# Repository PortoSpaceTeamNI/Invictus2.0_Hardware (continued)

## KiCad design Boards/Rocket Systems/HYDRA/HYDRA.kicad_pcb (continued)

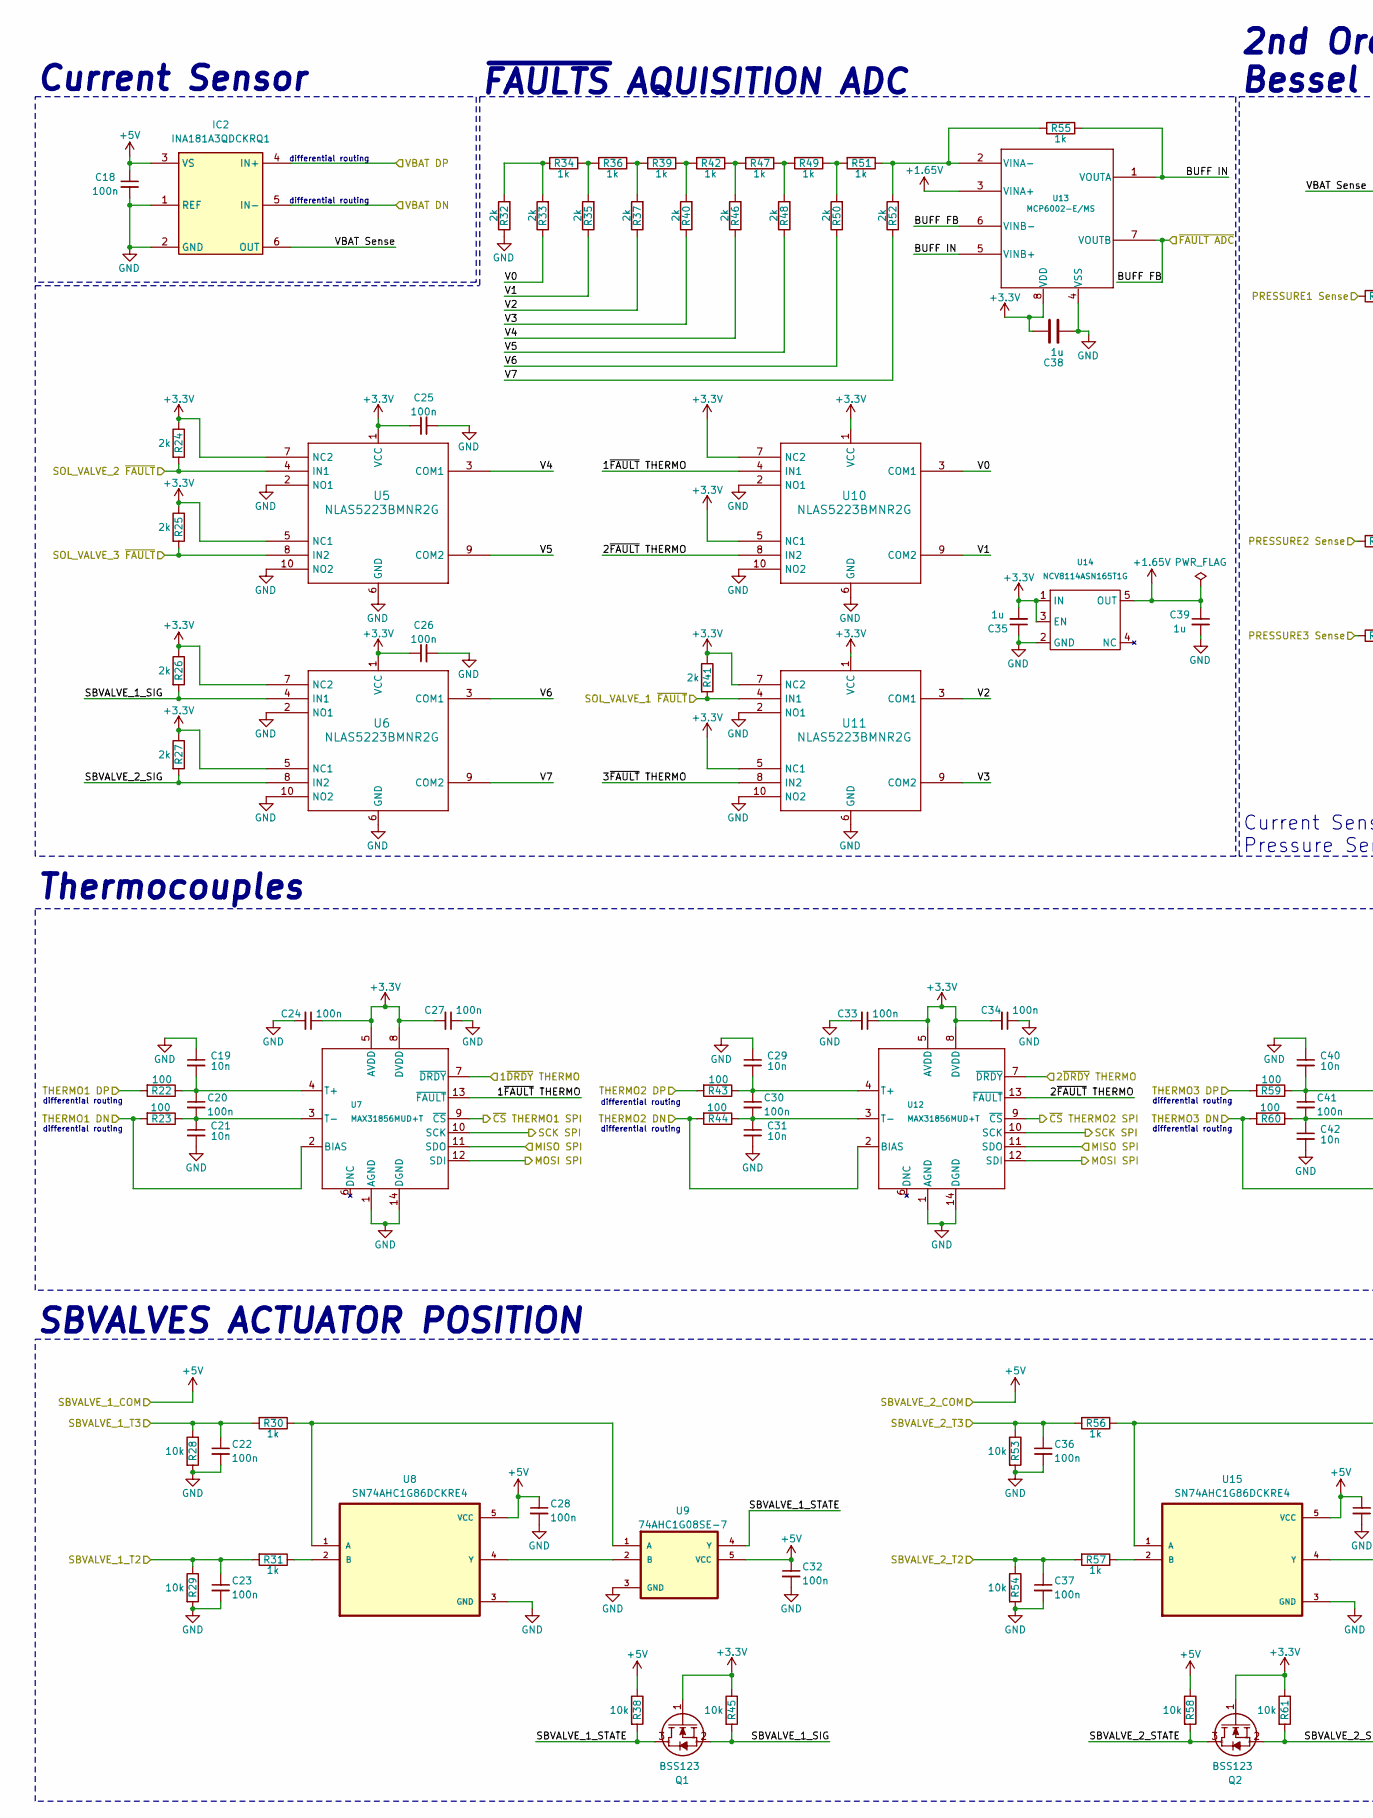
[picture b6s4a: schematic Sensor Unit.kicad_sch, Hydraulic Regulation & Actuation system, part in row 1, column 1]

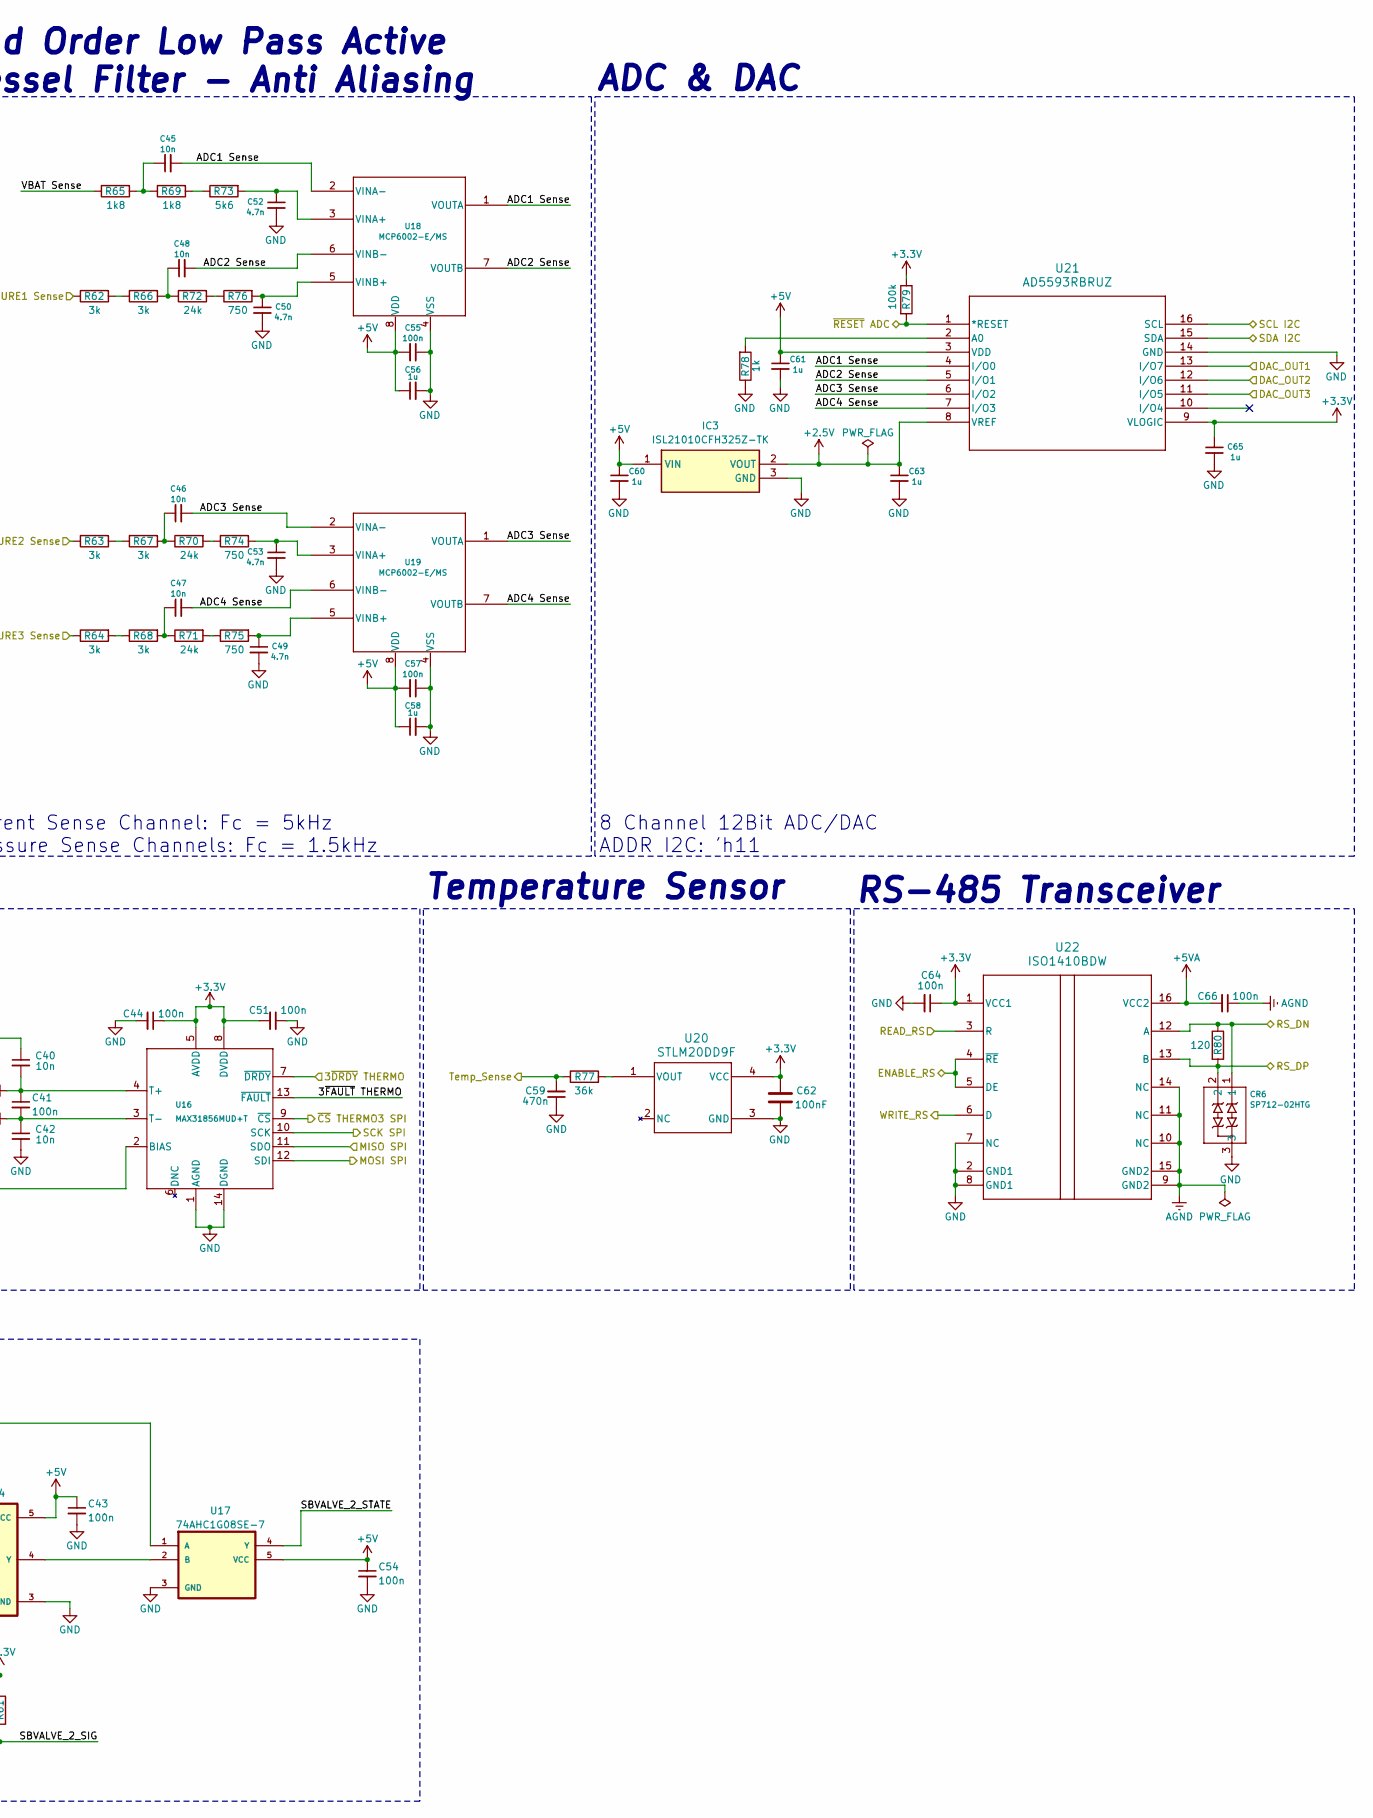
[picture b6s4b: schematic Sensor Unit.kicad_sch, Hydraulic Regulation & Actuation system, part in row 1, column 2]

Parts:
C18, C20, C22, C23, C24, C25, C26, C27, C28, C30, C32, C33, C34, C36, C37, C41, C43, C44, C51, C54, C55, C57, C64, C66: 100n; Capacitor_0402
C19, C21, C29, C31, C40, C42, C45, C46, C47, C48: 10n; Capacitor_0402
C35, C38, C39, C56, C58, C60, C61, C63, C65: 1u; Capacitor_0603
C49, C50, C52, C53: 4.7n; Capacitor_0402
C59: 470n; Capacitor_0402
C62: 100nF; Capacitor_0402
CR6: SP712-02HTG; SOT23-3_LTF
IC2: INA181A3QDCKRQ1; SOT65P210X110-6N; Mouser Part Number 595-INA181A3QDCKRQ1
IC3: ISL21010CFH325Z-TK; SOT95P237X112-3N; Mouser Part Number 968-ISL21010CFH325ZT
Q1, Q2: BSS123; SOT96P237X111-3N; Mouser Part Number 512-BSS123
R22, R23, R43, R44, R59, R60: 100; RES_0402
R24, R25, R26, R27, R32, R33, R35, R37, R40, R41, R46, R48, R50, R52: 2k; RES_0402
R28, R29, R38, R45, R53, R54, R58, R61: 10k; RES_0402
R30, R31, R34, R36, R39, R42, R47, R49, R51, R55, R56, R57, R78: 1k; RES_0402
R62, R63, R64, R66, R67, R68: 3k; RES_0402
R65, R69: 1k8; RES_0402
R70, R71, R72: 24k; RES_0402
R73: 5k6; RES_0402
R74, R75, R76: 750; RES_0402
R77: 36k; RES_0402
R79: 100k; RES_0402
R80: 120; RES_0603
U5, U6, U10, U11: NLAS5223BMNR2G; WQFN10_1P4X1P8_ONS
U7, U12, U16: MAX31856MUD+T; 21-0066J_14_MXM
U8, U15: SN74AHC1G86DCKRE4; SOT65P210X110-5N
U9, U17: 74AHC1G08SE-7; SOT65P210X110-5N; MPN 74AHC1G08SE-7
U13, U18, U19: MCP6002-E/MS; MSOP8_MC_MCH
U14: NCV8114ASN165T1G; SOT95P275X120-5N
U20: STLM20DD9F; UDFN-4L_STM
U21: AD5593RBRUZ; RU-16_ADI-L
U22: ISO1410BDW; DW0016B_L

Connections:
+1.65V: C39.1, U13.3 (VINA+), U14.5 (OUT)
+2.5V: C63.1, IC3.2 (VOUT), U21.8 (VREF)
+3.3V: C24.1, C25.1, C26.1, C27.2, C33.1, C34.2, C35.2, C38.1, C44.1, C51.2, C62.1, C64.1, C65.1, Q1.1 (G), Q2.1 (G), R24.1, R25.1, R26.1, R27.1, R41.1, R45.1, R61.1, R79.1, U5.1 (VCC), U5.5 (NC1), U5.7 (NC2), U6.1 (VCC), U6.5 (NC1), U6.7 (NC2), U7.5 (AVDD), U7.8 (DVDD), U10.1 (VCC), U10.5 (NC1), U10.7 (NC2), U11.1 (VCC), U11.5 (NC1), U11.7 (NC2), U12.5 (AVDD), U12.8 (DVDD), U13.8 (VDD), U14.1 (IN), U14.3 (EN), U16.5 (AVDD), U16.8 (DVDD), U20.4 (VCC), U21.9 (VLOGIC), U22.1 (VCC1); also elsewhere on the board
+5V: C18.1, C28.1, C32.1, C43.1, C54.1, C55.2, C56.1, C57.2, C58.1, C60.1, C61.1, IC2.3 (VS), IC3.1 (VIN), R38.1, R58.1, U8.5 (VCC), U9.5 (VCC), U15.5 (VCC), U17.5 (VCC), U18.8 (VDD), U19.8 (VDD), U21.3 (VDD); also elsewhere on the board
+5VA: C66.2, U22.16 (VCC2); also elsewhere on the board
/1~DRDY THERMO: U7.7 (~DRDY); also elsewhere on the board
/2~DRDY THERMO: U12.7 (~DRDY); also elsewhere on the board
/3~DRDY THERMO: U16.7 (~DRDY); also elsewhere on the board
/Actuation Unit/SOL_VALVE_1 DUTY: U21.13 (I/O7); also elsewhere on the board
/Actuation Unit/SOL_VALVE_1 ~FAULT: R25.2, U5.8 (IN2); also elsewhere on the board
/Actuation Unit/SOL_VALVE_2 DUTY: U21.12 (I/O6); also elsewhere on the board
/Actuation Unit/SOL_VALVE_2 ~FAULT: R24.2, U5.4 (IN1); also elsewhere on the board
/Actuation Unit/SOL_VALVE_3 DUTY: U21.11 (I/O5); also elsewhere on the board
/Actuation Unit/SOL_VALVE_3 ~FAULT: R41.2, U11.4 (IN1); also elsewhere on the board
/ENABLE_RS: U22.4 (~RE), U22.5 (DE); also elsewhere on the board
/IO Connectors/PRESSURE1 Sense: R62.1; also elsewhere on the board
/IO Connectors/PRESSURE2 Sense: R63.1; also elsewhere on the board
/IO Connectors/PRESSURE3 Sense: R64.1; also elsewhere on the board
/IO Connectors/RS_DN: CR6.1, R80.1, U22.12 (A); also elsewhere on the board
/IO Connectors/RS_DP: CR6.2, R80.2, U22.13 (B); also elsewhere on the board
/IO Connectors/SBVALVE_1_T2: C23.1, R29.1, R31.2; also elsewhere on the board
/IO Connectors/SBVALVE_1_T3: C22.1, R28.1, R30.2; also elsewhere on the board
/IO Connectors/SBVALVE_2_T2: C37.1, R54.1, R57.2; also elsewhere on the board
/IO Connectors/SBVALVE_2_T3: C36.1, R53.1, R56.2; also elsewhere on the board
/IO Connectors/THERMO1 DN: R23.2, U7.2 (BIAS); also elsewhere on the board
/IO Connectors/THERMO1 DP: R22.2; also elsewhere on the board
/IO Connectors/THERMO2 DN: R44.2, U12.2 (BIAS); also elsewhere on the board
/IO Connectors/THERMO2 DP: R43.2; also elsewhere on the board
/IO Connectors/THERMO3 DN: R60.2, U16.2 (BIAS); also elsewhere on the board
/IO Connectors/THERMO3 DP: R59.2; also elsewhere on the board
/MISO SPI: U7.11 (SDO), U12.11 (SDO), U16.11 (SDO); also elsewhere on the board
/MOSI SPI: U7.12 (SDI), U12.12 (SDI), U16.12 (SDI); also elsewhere on the board
/PCB Temperature Sense: C59.2, R77.1; also elsewhere on the board
/Power Unit/VBAT DP: IC2.4 (IN+); also elsewhere on the board
/READ_RS: U22.3 (R); also elsewhere on the board
/RP2040 Standard/GP14/I2C1 SDA: U21.15 (SDA); also elsewhere on the board
/RP2040 Standard/GP15/I2C1 SCL: U21.16 (SCL); also elsewhere on the board
/RP2040 Standard/GPIO16: R79.2, U21.1 (*RESET); also elsewhere on the board
/SCK SPI: U7.10 (SCK), U12.10 (SCK), U16.10 (SCK); also elsewhere on the board
/Sensor Unit/1~FAULT THERMO: U7.13 (~FAULT), U10.4 (IN1)
/Sensor Unit/2~FAULT THERMO: U10.8 (IN2), U12.13 (~FAULT)
/Sensor Unit/3~FAULT THERMO: U11.8 (IN2), U16.13 (~FAULT)
/Sensor Unit/ADC1 Sense: C45.2, U18.1 (VOUTA), U18.2 (VINA-), U21.4 (I/O0)
/Sensor Unit/ADC2 Sense: C48.2, U18.6 (VINB-), U18.7 (VOUTB), U21.5 (I/O1)
/Sensor Unit/ADC3 Sense: C46.2, U19.1 (VOUTA), U19.2 (VINA-), U21.6 (I/O2)
/Sensor Unit/ADC4 Sense: C47.2, U19.6 (VINB-), U19.7 (VOUTB), U21.7 (I/O3)
/Sensor Unit/BUFF FB: U13.6 (VINB-), U13.7 (VOUTB); also elsewhere on the board
/Sensor Unit/BUFF IN: R55.1, U13.1 (VOUTA), U13.5 (VINB+)
/Sensor Unit/SBVALVE_1_SIG: Q1.2 (S), R26.2, R45.2, U6.4 (IN1)
/Sensor Unit/SBVALVE_1_STATE: Q1.3 (D), R38.2, U9.4 (Y)
/Sensor Unit/SBVALVE_2_SIG: Q2.2 (S), R27.2, R61.2, U6.8 (IN2)
/Sensor Unit/SBVALVE_2_STATE: Q2.3 (D), R58.2, U17.4 (Y)
/Sensor Unit/V0: R33.1, U10.3 (COM1)
/Sensor Unit/V1: R35.1, U10.9 (COM2)
/Sensor Unit/V2: R37.1, U11.3 (COM1)
/Sensor Unit/V3: R40.1, U11.9 (COM2)
/Sensor Unit/V4: R46.1, U5.3 (COM1)
/Sensor Unit/V5: R48.1, U5.9 (COM2)
/Sensor Unit/V6: R50.1, U6.3 (COM1)
/Sensor Unit/V7: R52.1, U6.9 (COM2)
/Sensor Unit/VBAT Sense: IC2.6 (OUT), R65.1
/WRITE_RS: U22.6 (D); also elsewhere on the board
/~CS THERMO1 SPI: U7.9 (~CS); also elsewhere on the board
/~CS THERMO2 SPI: U12.9 (~CS); also elsewhere on the board
/~CS THERMO3 SPI: U16.9 (~CS); also elsewhere on the board
AGND: C66.1, U22.9 (GND2), U22.10 (NC), U22.11 (NC), U22.14 (NC), U22.15 (GND2); also elsewhere on the board
GND: C18.2, C19.1, C21.2, C22.2, C23.2, C24.2, C25.2, C26.2, C27.1, C28.2, C29.1, C31.2, C32.2, C33.2, C34.1, C35.1, C36.2, C37.2, C38.2, C39.2, C40.1, C42.2, C43.2, C44.2, C49.2, C50.2, C51.1, C52.2, C53.2, C54.2, C55.1, C56.2, C57.1, C58.2, C59.1, C60.2, C61.2, C62.2, C63.2, C64.2, C65.2, CR6.3, IC2.1 (REF), IC2.2 (GND), IC3.3 (GND), R28.2, R29.2, R32.1, R53.2, R54.2, R78.1, U5.2 (NO1), U5.6 (GND), U5.10 (NO2), U6.2 (NO1), U6.6 (GND), U6.10 (NO2), U7.1 (AGND), U7.14 (DGND), U8.3 (GND), U9.3 (GND), U10.2 (NO1), U10.6 (GND), U10.10 (NO2), U11.2 (NO1), U11.6 (GND), U11.10 (NO2), U12.1 (AGND), U12.14 (DGND), U13.4 (VSS), U14.2 (GND), U15.3 (GND), U16.1 (AGND), U16.14 (DGND), U17.3 (GND), U18.4 (VSS), U19.4 (VSS), U20.3 (GND), U21.14 (GND), U22.2 (GND1), U22.7 (NC), U22.8 (GND1); also elsewhere on the board
unnamed: C45.1, R65.2, R69.1
unnamed: C46.1, R67.2, R70.1
unnamed: C47.1, R68.2, R71.1
unnamed: C48.1, R66.2, R72.1
unnamed: R32.2, R33.2, R34.2
unnamed: R34.1, R35.2, R36.2
unnamed: R36.1, R37.2, R39.2
unnamed: R39.1, R40.2, R42.2
unnamed: R42.1, R46.2, R47.2
unnamed: R47.1, R48.2, R49.2
unnamed: R49.1, R50.2, R51.2
unnamed: R62.2, R66.1
unnamed: R63.2, R67.1
unnamed: R64.2, R68.1
unnamed: R69.2, R73.1
unnamed: R70.2, R74.1
unnamed: R71.2, R75.1
unnamed: R72.2, R76.1
unnamed: C19.2, C20.1, R22.1, U7.4 (T+)
unnamed: C20.2, C21.1, R23.1, U7.3 (T-)
unnamed: R30.1, U8.1 (A), U9.1 (A)
unnamed: R31.1, U8.2 (B)
unnamed: U8.4 (Y), U9.2 (B)
unnamed: C29.2, C30.1, R43.1, U12.4 (T+)
unnamed: C30.2, C31.1, R44.1, U12.3 (T-)
unnamed: R51.1, R52.2, R55.2, U13.2 (VINA-)
unnamed: R56.1, U15.1 (A), U17.1 (A)
unnamed: R57.1, U15.2 (B)
unnamed: U15.4 (Y), U17.2 (B)
unnamed: C40.2, C41.1, R59.1, U16.4 (T+)
unnamed: C41.2, C42.1, R60.1, U16.3 (T-)
unnamed: C52.1, R73.2, U18.3 (VINA+)
unnamed: C50.1, R76.2, U18.5 (VINB+)
unnamed: C53.1, R74.2, U19.3 (VINA+)
unnamed: C49.1, R75.2, U19.5 (VINB+)
unnamed: R77.2, U20.1 (VOUT)
unnamed: R78.2, U21.2 (A0)
VDC: IC2.5 (IN-); also elsewhere on the board

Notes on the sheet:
differential routing
Current Sensor
SBVALVES ACTUATOR POSITION
8 Channel 12Bit ADC/DAC ADDR I2C: 'h11
Current Sense Channel: Fc = 5kHz Pressure Sense Channels: Fc = 1.5kHz
RS-485 Transceiver
~{FAULTS} AQUISITION ADC
Thermocouples
2nd Order Low Pass Active Bessel Filter - Anti Aliasing
ADC & DAC
Temperature Sensor

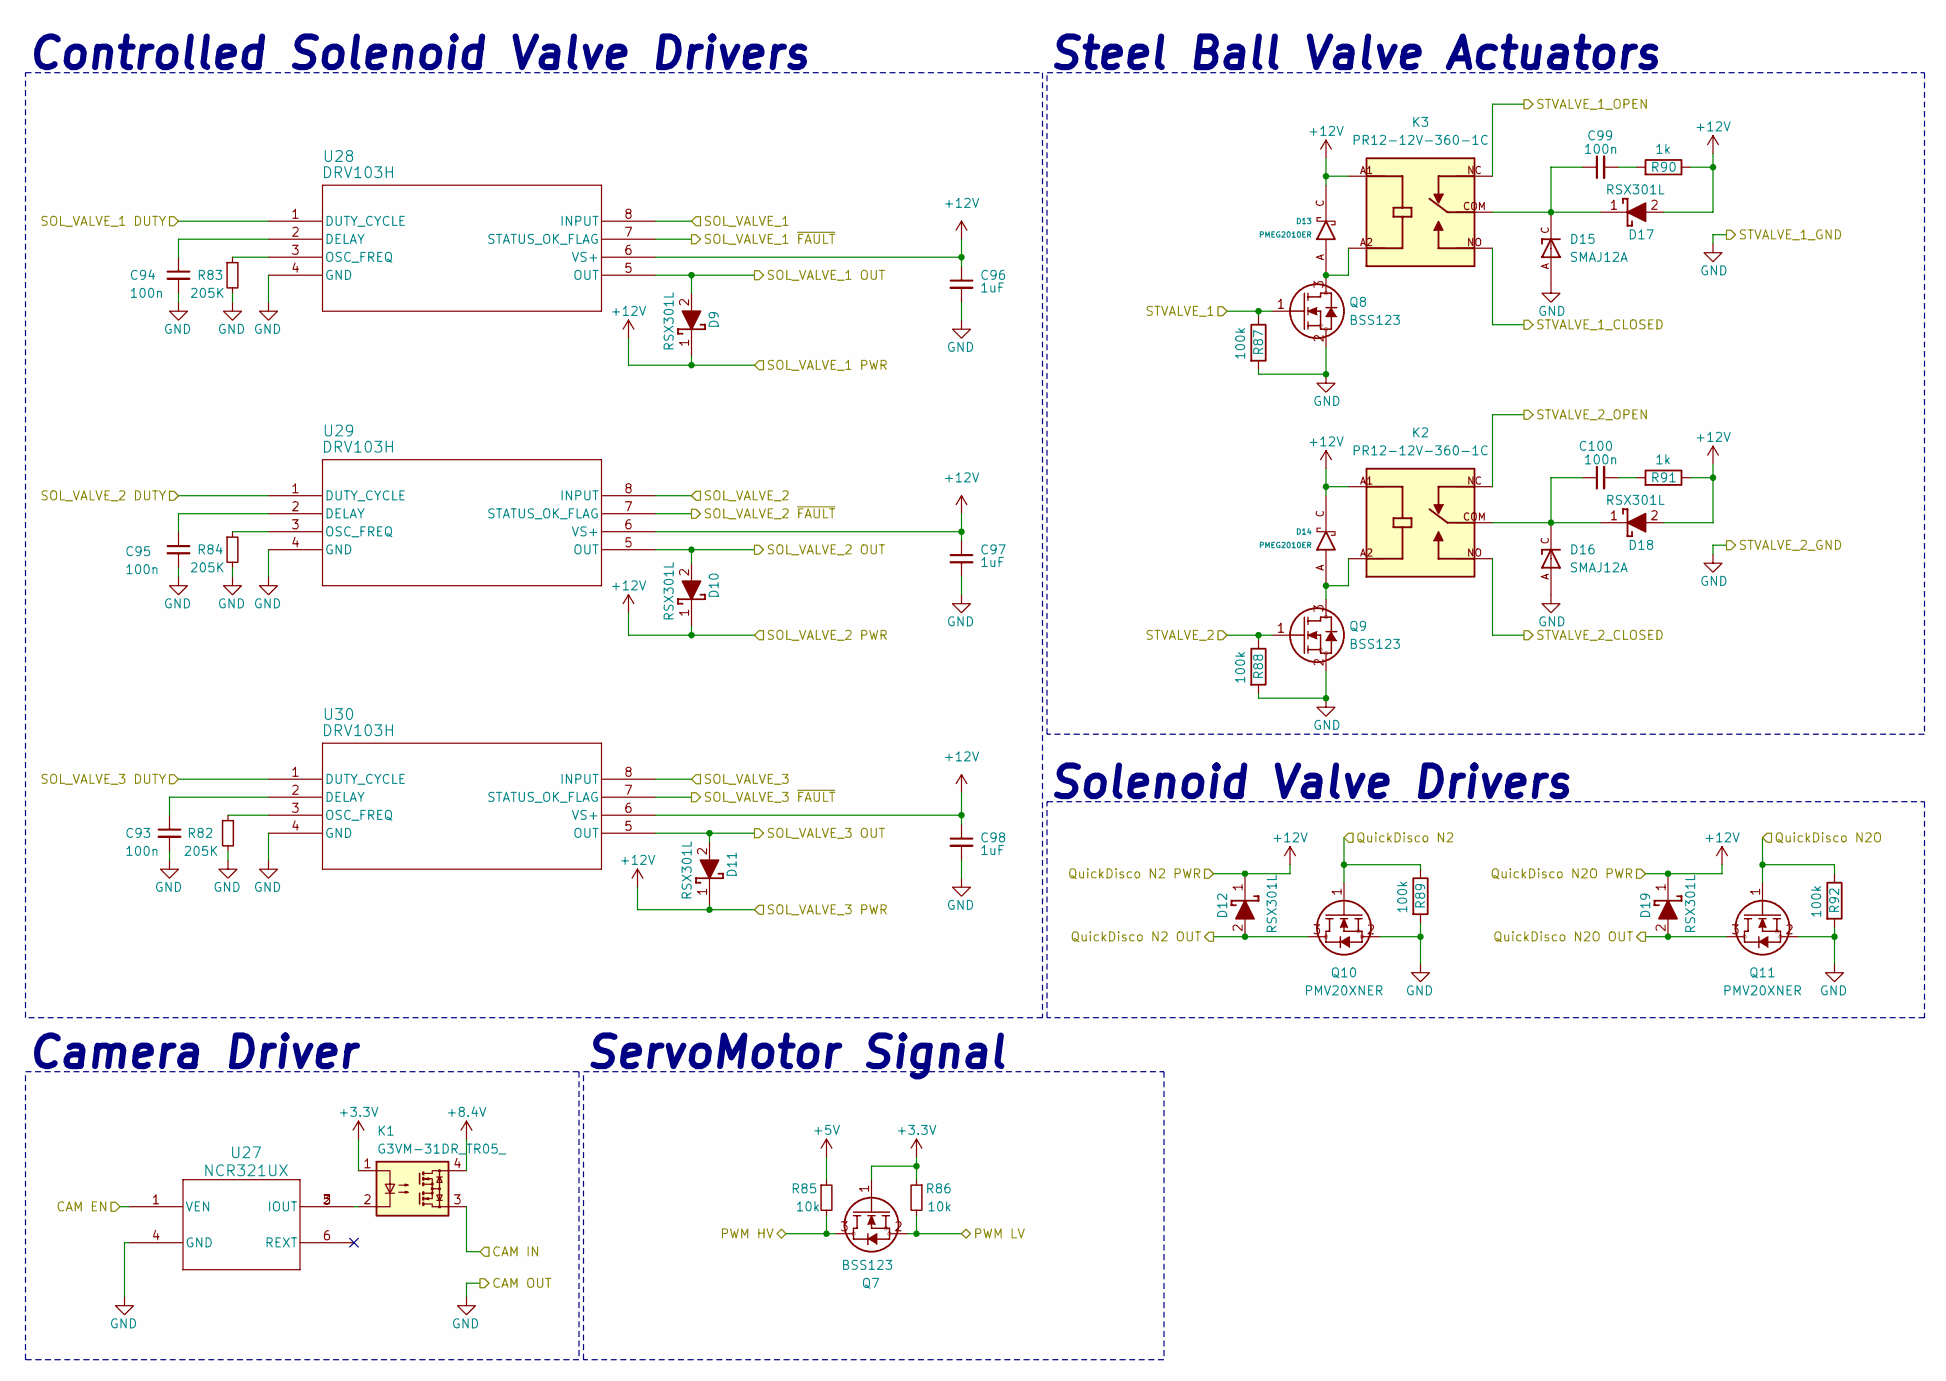
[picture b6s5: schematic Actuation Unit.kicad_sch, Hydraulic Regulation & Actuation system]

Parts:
C93, C94, C95: 100n; Capacitor_0402
C96, C97, C98: 1uF; Capacitor_0603
C99, C100: 100n; Capacitor_0603
D9, D10, D11, D12, D17, D18, D19: RSX301L; DIOM5026X220N; Mouser Part Number 755-RSX301L-30DDTE25
D13, D14: PMEG2010ER; SODFL3517X110N; PARTREV 01
D15, D16: SMAJ12A; DIOM4325X250N; PARTREV S2102
K1: G3VM-31DR_TR05_; G3VM31DRTR05; Mouser Part Number 653-G3VM-31DR(TR05)
K2, K3: PR12-12V-360-1C; RELAY_PR12-12V-360-1C; PARTREV 1.0
Q7, Q8, Q9: BSS123; SOT96P237X111-3N; Mouser Part Number 512-BSS123
Q10, Q11: PMV20XNER; SOT95P230X110-3N; Mouser Part Number 771-PMV20XNER
R82, R83, R84: 205K; RES_0402
R85, R86: 10k; RES_0402
R87, R88, R89, R92: 100k; RES_0402
R90, R91: 1k; RES_0805
U27: NCR321UX; TSOP6_SOT457_NEX
U28, U29, U30: DRV103H; DDA8-L

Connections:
+3.3V: K1.1, Q7.1 (G), R86.1; also elsewhere on the board
+5V: R85.1; also elsewhere on the board
+8.4V: K1.4; also elsewhere on the board
+12V: C96.1, C97.1, C98.1, D9.1 (K), D10.1 (K), D11.1 (K), D12.1 (K), D13.C, D14.C, D17.2 (A), D18.2 (A), D19.1 (K), K2.A1, K3.A1, R90.1, R91.1, U28.6 (VS+), U29.6 (VS+), U30.6 (VS+); also elsewhere on the board
/Actuation Unit/CAM EN: U27.1 (VEN); also elsewhere on the board
/Actuation Unit/CAM IN: K1.3; also elsewhere on the board
/Actuation Unit/PWM HV: Q7.3 (D), R85.2; also elsewhere on the board
/Actuation Unit/PWM LV: Q7.2 (S), R86.2; also elsewhere on the board
/Actuation Unit/QuickDisco N2: Q10.1 (G), R89.1; also elsewhere on the board
/Actuation Unit/QuickDisco N2 OUT: D12.2 (A), Q10.3 (D); also elsewhere on the board
/Actuation Unit/QuickDisco N2O: Q11.1 (G), R92.1; also elsewhere on the board
/Actuation Unit/QuickDisco N2O OUT: D19.2 (A), Q11.3 (D); also elsewhere on the board
/Actuation Unit/SOL_VALVE_1: U28.8 (INPUT); also elsewhere on the board
/Actuation Unit/SOL_VALVE_1 DUTY: U28.1 (DUTY_CYCLE); also elsewhere on the board
/Actuation Unit/SOL_VALVE_1 OUT: D9.2 (A), U28.5 (OUT); also elsewhere on the board
/Actuation Unit/SOL_VALVE_1 ~FAULT: U28.7 (STATUS_OK_FLAG); also elsewhere on the board
/Actuation Unit/SOL_VALVE_2: U29.8 (INPUT); also elsewhere on the board
/Actuation Unit/SOL_VALVE_2 DUTY: U29.1 (DUTY_CYCLE); also elsewhere on the board
/Actuation Unit/SOL_VALVE_2 OUT: D10.2 (A), U29.5 (OUT); also elsewhere on the board
/Actuation Unit/SOL_VALVE_2 ~FAULT: U29.7 (STATUS_OK_FLAG); also elsewhere on the board
/Actuation Unit/SOL_VALVE_3: U30.8 (INPUT); also elsewhere on the board
/Actuation Unit/SOL_VALVE_3 DUTY: U30.1 (DUTY_CYCLE); also elsewhere on the board
/Actuation Unit/SOL_VALVE_3 OUT: D11.2 (A), U30.5 (OUT); also elsewhere on the board
/Actuation Unit/SOL_VALVE_3 ~FAULT: U30.7 (STATUS_OK_FLAG); also elsewhere on the board
/Actuation Unit/STVALVE_1: Q8.1 (G), R87.1; also elsewhere on the board
/Actuation Unit/STVALVE_1_CLOSED: K3.NO; also elsewhere on the board
/Actuation Unit/STVALVE_1_OPEN: K3.NC; also elsewhere on the board
/Actuation Unit/STVALVE_2: Q9.1 (G), R88.1; also elsewhere on the board
/Actuation Unit/STVALVE_2_CLOSED: K2.NO; also elsewhere on the board
/Actuation Unit/STVALVE_2_OPEN: K2.NC; also elsewhere on the board
GND: C93.2, C94.2, C95.2, C96.2, C97.2, C98.2, D15.A, D16.A, Q8.2 (S), Q9.2 (S), Q10.2 (S), Q11.2 (S), R82.2, R83.2, R84.2, R87.2, R88.2, R89.2, R92.2, U27.4 (GND), U28.4 (GND), U29.4 (GND), U30.4 (GND); also elsewhere on the board
unnamed: C99.2, R90.2
unnamed: C100.2, R91.2
unnamed: C99.1, D15.C, D17.1 (K), K3.COM
unnamed: C100.1, D16.C, D18.1 (K), K2.COM
unnamed: K1.2, U27.2 (IOUT), U27.3 (IOUT), U27.5 (IOUT)
unnamed: D13.A, K3.A2, Q8.3 (D)
unnamed: D14.A, K2.A2, Q9.3 (D)
unnamed: C94.1, U28.2 (DELAY)
unnamed: R83.1, U28.3 (OSC_FREQ)
unnamed: C95.1, U29.2 (DELAY)
unnamed: R84.1, U29.3 (OSC_FREQ)
unnamed: C93.1, U30.2 (DELAY)
unnamed: R82.1, U30.3 (OSC_FREQ)

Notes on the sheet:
Solenoid Valve Drivers
Controlled Solenoid Valve Drivers
Camera Driver
ServoMotor Signal
Steel Ball Valve Actuators

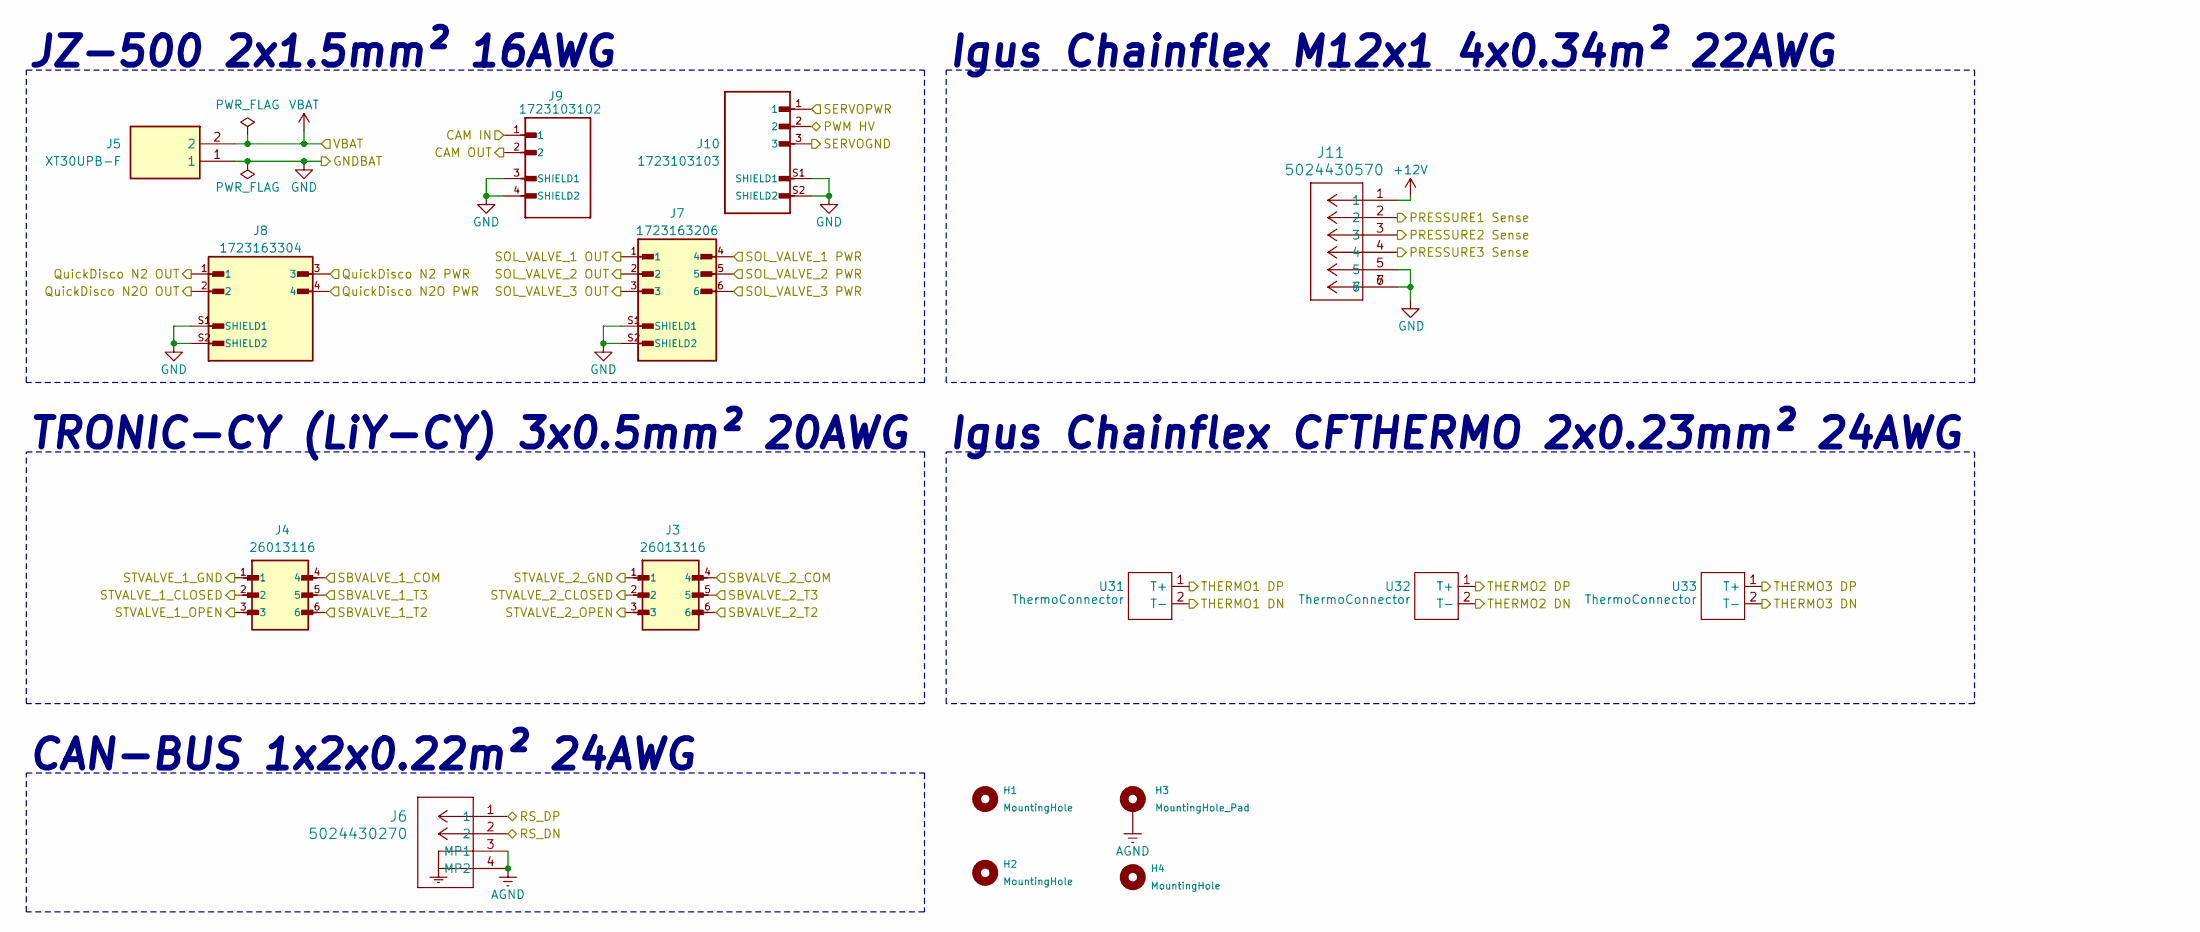
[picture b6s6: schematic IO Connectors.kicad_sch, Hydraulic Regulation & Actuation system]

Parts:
H1, H2, H4: MountingHole; MountingHole_3.2mm_M3_ISO7380
H3: MountingHole_Pad; MountingHole_3.2mm_M3_ISO7380_Pad
J3, J4: 26013116; MOLEX_26013116; PARTREV A
J5: XT30UPB-F; XT30UPBF; Manufacturer_Part_Number XT30UPB-F
J6: 5024430270; CONN_502443-02xx_MOL
J7: 1723163206; MOLEX_1723163206; PARTREV D
J8: 1723163304; MOLEX_1723163304; PARTREV D
J9: 1723103102; CONN02_1723103102_MOL; MANUFACTURER_PART_NUMBER 1723103102; DigiKey_Part_Number 900-1723103102-ND
J10: 1723103103; MOLEX_1723103103; PARTREV B1; DigiKey_Part_Number 900-1723103103-ND
J11: 5024430570; CONN_502443-05xx_MOL
U31, U32, U33: ThermoConnector; Thermo Type K PCB Connector

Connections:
+5V: J3.4, J4.4; also elsewhere on the board
+8.4V: J10.1; also elsewhere on the board
+12V: J7.4, J7.5, J7.6, J8.3, J8.4, J11.1; also elsewhere on the board
/Actuation Unit/CAM IN: J9.1; also elsewhere on the board
/Actuation Unit/PWM HV: J10.2; also elsewhere on the board
/Actuation Unit/QuickDisco N2 OUT: J8.1; also elsewhere on the board
/Actuation Unit/QuickDisco N2O OUT: J8.2; also elsewhere on the board
/Actuation Unit/SOL_VALVE_1 OUT: J7.1; also elsewhere on the board
/Actuation Unit/SOL_VALVE_2 OUT: J7.2; also elsewhere on the board
/Actuation Unit/SOL_VALVE_3 OUT: J7.3; also elsewhere on the board
/Actuation Unit/STVALVE_1_CLOSED: J4.2; also elsewhere on the board
/Actuation Unit/STVALVE_1_OPEN: J4.3; also elsewhere on the board
/Actuation Unit/STVALVE_2_CLOSED: J3.2; also elsewhere on the board
/Actuation Unit/STVALVE_2_OPEN: J3.3; also elsewhere on the board
/IO Connectors/PRESSURE1 Sense: J11.2; also elsewhere on the board
/IO Connectors/PRESSURE2 Sense: J11.3; also elsewhere on the board
/IO Connectors/PRESSURE3 Sense: J11.4; also elsewhere on the board
/IO Connectors/RS_DN: J6.2; also elsewhere on the board
/IO Connectors/RS_DP: J6.1; also elsewhere on the board
/IO Connectors/SBVALVE_1_T2: J4.6; also elsewhere on the board
/IO Connectors/SBVALVE_1_T3: J4.5; also elsewhere on the board
/IO Connectors/SBVALVE_2_T2: J3.6; also elsewhere on the board
/IO Connectors/SBVALVE_2_T3: J3.5; also elsewhere on the board
/IO Connectors/THERMO1 DN: U31.2 (T-); also elsewhere on the board
/IO Connectors/THERMO1 DP: U31.1 (T+); also elsewhere on the board
/IO Connectors/THERMO2 DN: U32.2 (T-); also elsewhere on the board
/IO Connectors/THERMO2 DP: U32.1 (T+); also elsewhere on the board
/IO Connectors/THERMO3 DN: U33.2 (T-); also elsewhere on the board
/IO Connectors/THERMO3 DP: U33.1 (T+); also elsewhere on the board
AGND: H3.1, J6.3 (MP1), J6.4 (MP2); also elsewhere on the board
GND: J3.1, J4.1, J5.1, J7.S1 (SHIELD1), J7.S2 (SHIELD2), J8.S1 (SHIELD1), J8.S2 (SHIELD2), J9.2, J9.3 (SHIELD1), J9.4 (SHIELD2), J10.3, J10.S1 (SHIELD1), J10.S2 (SHIELD2), J11.5, J11.6, J11.7; also elsewhere on the board
VBAT: J5.2; also elsewhere on the board

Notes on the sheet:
CAN-BUS 1x2x0.22m² 24AWG
TRONIC-CY (LiY-CY) 3x0.5mm² 20AWG
JZ-500 2x1.5mm² 16AWG
Igus Chainflex M12x1 4x0.34m² 22AWG
Igus Chainflex CFTHERMO 2x0.23mm² 24AWG

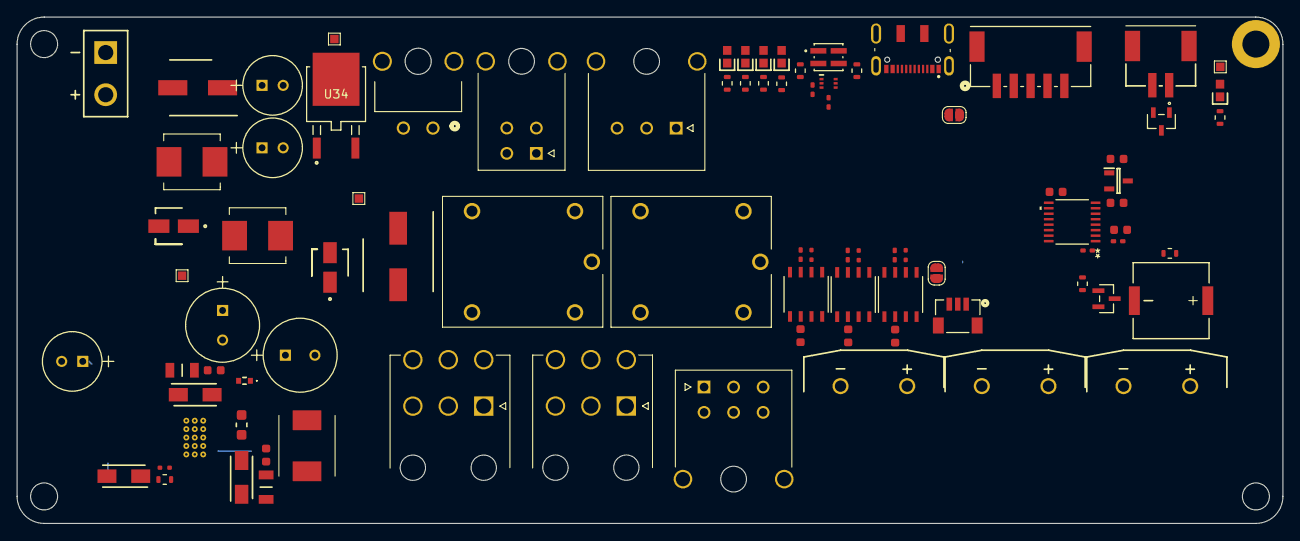
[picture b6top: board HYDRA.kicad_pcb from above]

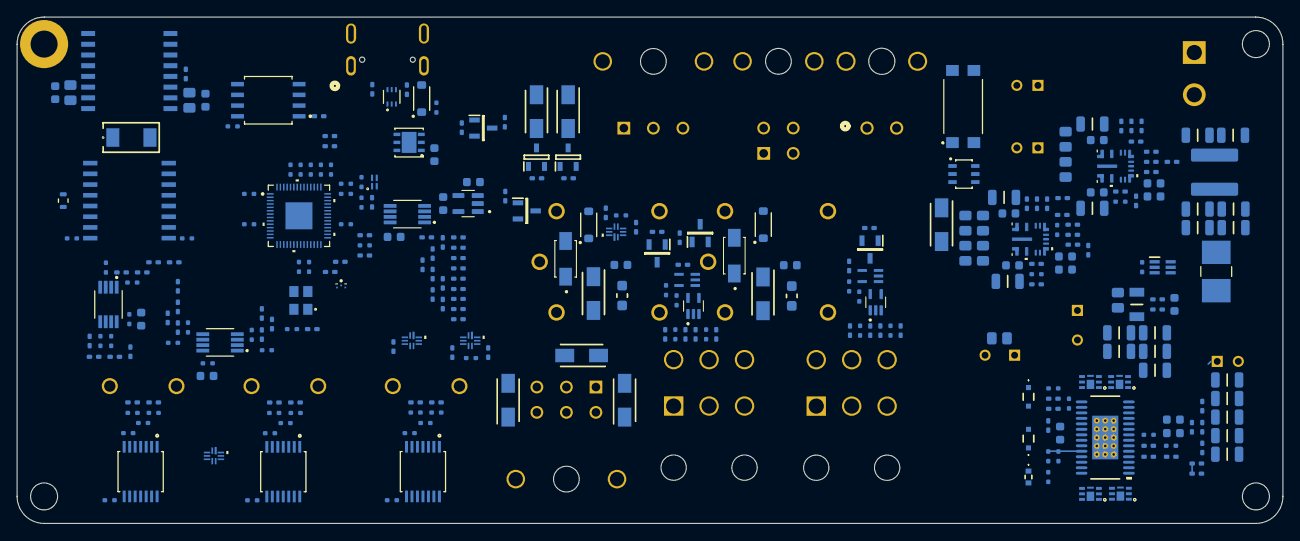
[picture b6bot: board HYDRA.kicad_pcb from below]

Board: 6 copper layers, 150.0 x 60.0 mm, 381 parts (290 on the bottom side), 234 nets.
